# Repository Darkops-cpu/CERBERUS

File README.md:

# Cerberus

An open-source iCE40 FPGA development board with a fully open toolchain.

No licence server, no 100 GB install. Yosys, nextpnr and IceStorm run on any laptop and
synthesise a design this size in seconds.

> **Status:** rev A, first boards in fabrication. Untested. Do not fabricate your own copy
> until this note is gone.

---

## Features

| | |
|---|---|
| **FPGA** | Lattice iCE40UP5K — 5,280 LUT4, 120 kbit BRAM, 1 Mbit SPRAM, 8 DSP blocks |
| **PSRAM** | 8 MB QSPI (LY68L6400SLIT) |
| **Flash** | 4 MB SPI configuration flash (W25Q32) |
| **Host** | FT2232HL — USB programming *and* a serial console over one cable |
| **Clock** | 12 MHz active oscillator into a global clock buffer |
| **Expansion** | 2× PMOD, 8 user GPIO on a 0.1" header |
| **LEDs** | 3 user RGB + power, USB and CDONE status |
| **Connector** | USB-C |
| **PCB** | 4-layer, hand-assembled |

The FT2232H's two channels run independently, so you can flash a bitstream and watch a UART
console at the same time without switching modes.

---

## Getting started

### 1. Install the toolchain

Download the [OSS CAD Suite](https://github.com/YosysHQ/oss-cad-suite-build/releases) and
add it to your `PATH`. That's Yosys, nextpnr, IceStorm, Icarus, Verilator, GTKWave and
`iceprog` in one archive. Nothing to compile, nothing to licence.

```sh
source <path-to-oss-cad-suite>/environment
```

### 2. Build

```sh
yosys -p 'synth_ice40 -top top -json top.json' top.v
nextpnr-ice40 --up5k --package sg48 --json top.json --pcf cerberus.pcf --asc top.asc
icepack top.asc top.bin
```

### 3. Flash

The config SPI is on the FT2232H's **channel B**, so the `-I B` flag is required:

```sh
iceprog -I B top.bin
```

The CDONE LED lights when configuration succeeds.

### 4. Console

Channel A enumerates as a second serial port. On Linux the two channels appear as
`/dev/ttyUSB0` (A) and `/dev/ttyUSB1` (B):

```sh
picocom -b 115200 /dev/ttyUSB0
```

---

## Pinout

Key pins. Everything else is in `cerberus.pcf`.

| Function | FPGA pin |
|---|---|
| 12 MHz clock in | 37 (G1) |
| UART TX (FPGA → host) | 18 |
| UART RX (host → FPGA) | 19 |
| PSRAM CE# | 6 |
| PSRAM SCK | 9 |
| PSRAM SIO0–3 | 10, 11, 12, 13 |
| RGB LEDs | 39, 40, 41 |
| CDONE | 7 |
| CRESET_B | 8 |

Pins 14–17 are the configuration SPI bus and are not available to user designs.

**Globals available on this package:** 35 (G0), 37 (G1), 20 (G3), 44 (G6). Put clocks on
these — a clock on an ordinary pin routes through general fabric with worse skew.

**RGB LEDs** are constant-current sinks driven by the `SB_RGBA_DRV` primitive. Current is
set in the IP, not by a resistor.

---

## Notes

**Reset.** The button pulls `CRESET_B` low and reconfigures the FPGA from flash on release.
Configuration takes under 140 ms.

**Internal oscillator.** The iCE40's internal 48 MHz `SB_HFOSC` is ±20% on industrial parts.
Fine for blinking an LED, useless for a UART — that's why the board has an external
oscillator. Use pin 37.

**PSRAM.** The controller must break long transfers into chunks and deassert CE# between
them — the part self-refreshes only while CE# is high, and holding it low past the tCEM
window loses data. Linear burst across page boundaries is not supported on this part.

**Powering.** Bus-powered from USB-C. There is no barrel jack and no external supply input.

---

## Licence

Hardware: [CERN-OHL-S v2](https://cern-ohl.web.cern.ch/)
Gateware and examples: MIT

---

## Acknowledgements

Built on the work of [YosysHQ](https://github.com/YosysHQ) and
[Project IceStorm](https://github.com/YosysHQ/icestorm). Pin conventions follow
[iCEBreaker](https://github.com/icebreaker-fpga/icebreaker), and the SG48 pinout is
documented in Lattice FPGA-UG-02001.

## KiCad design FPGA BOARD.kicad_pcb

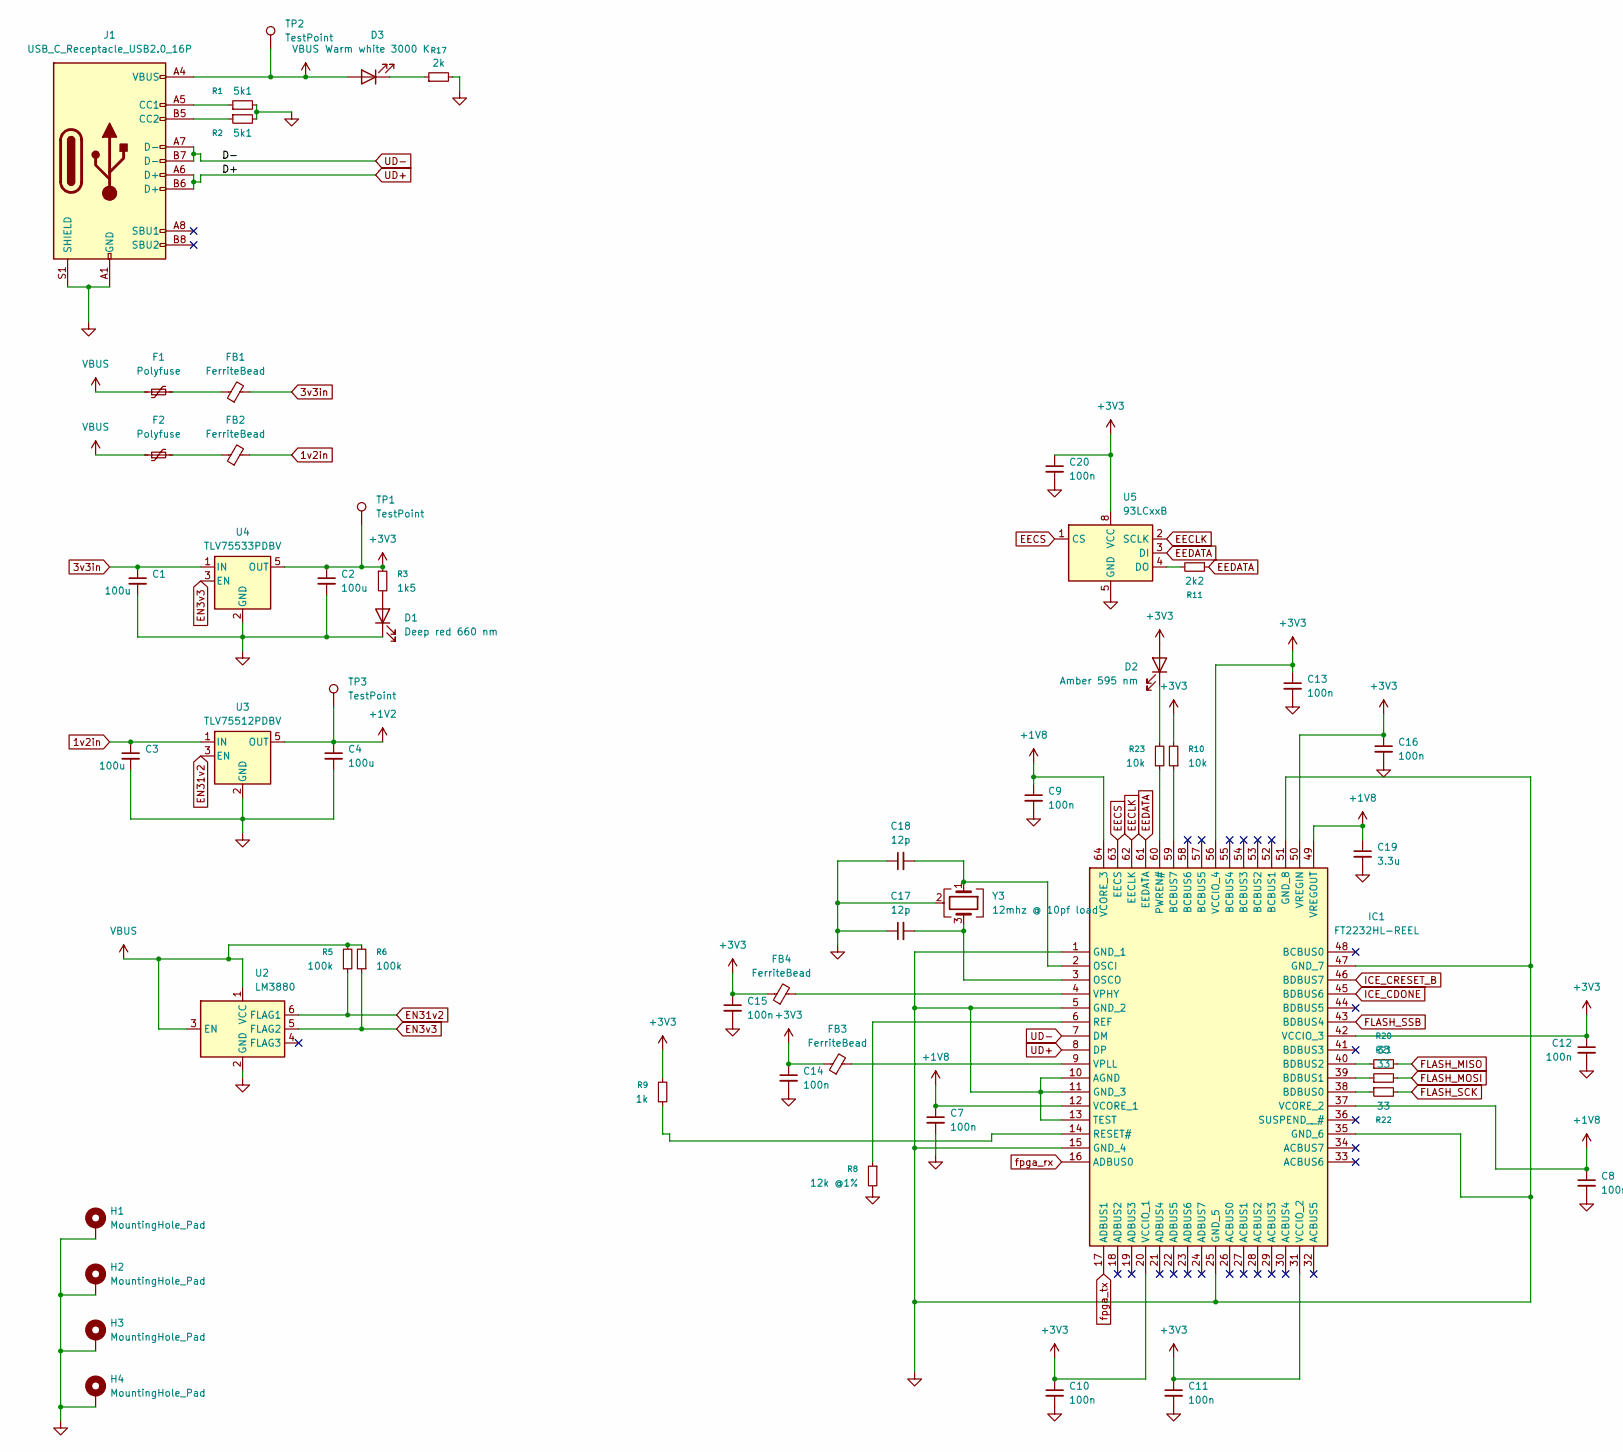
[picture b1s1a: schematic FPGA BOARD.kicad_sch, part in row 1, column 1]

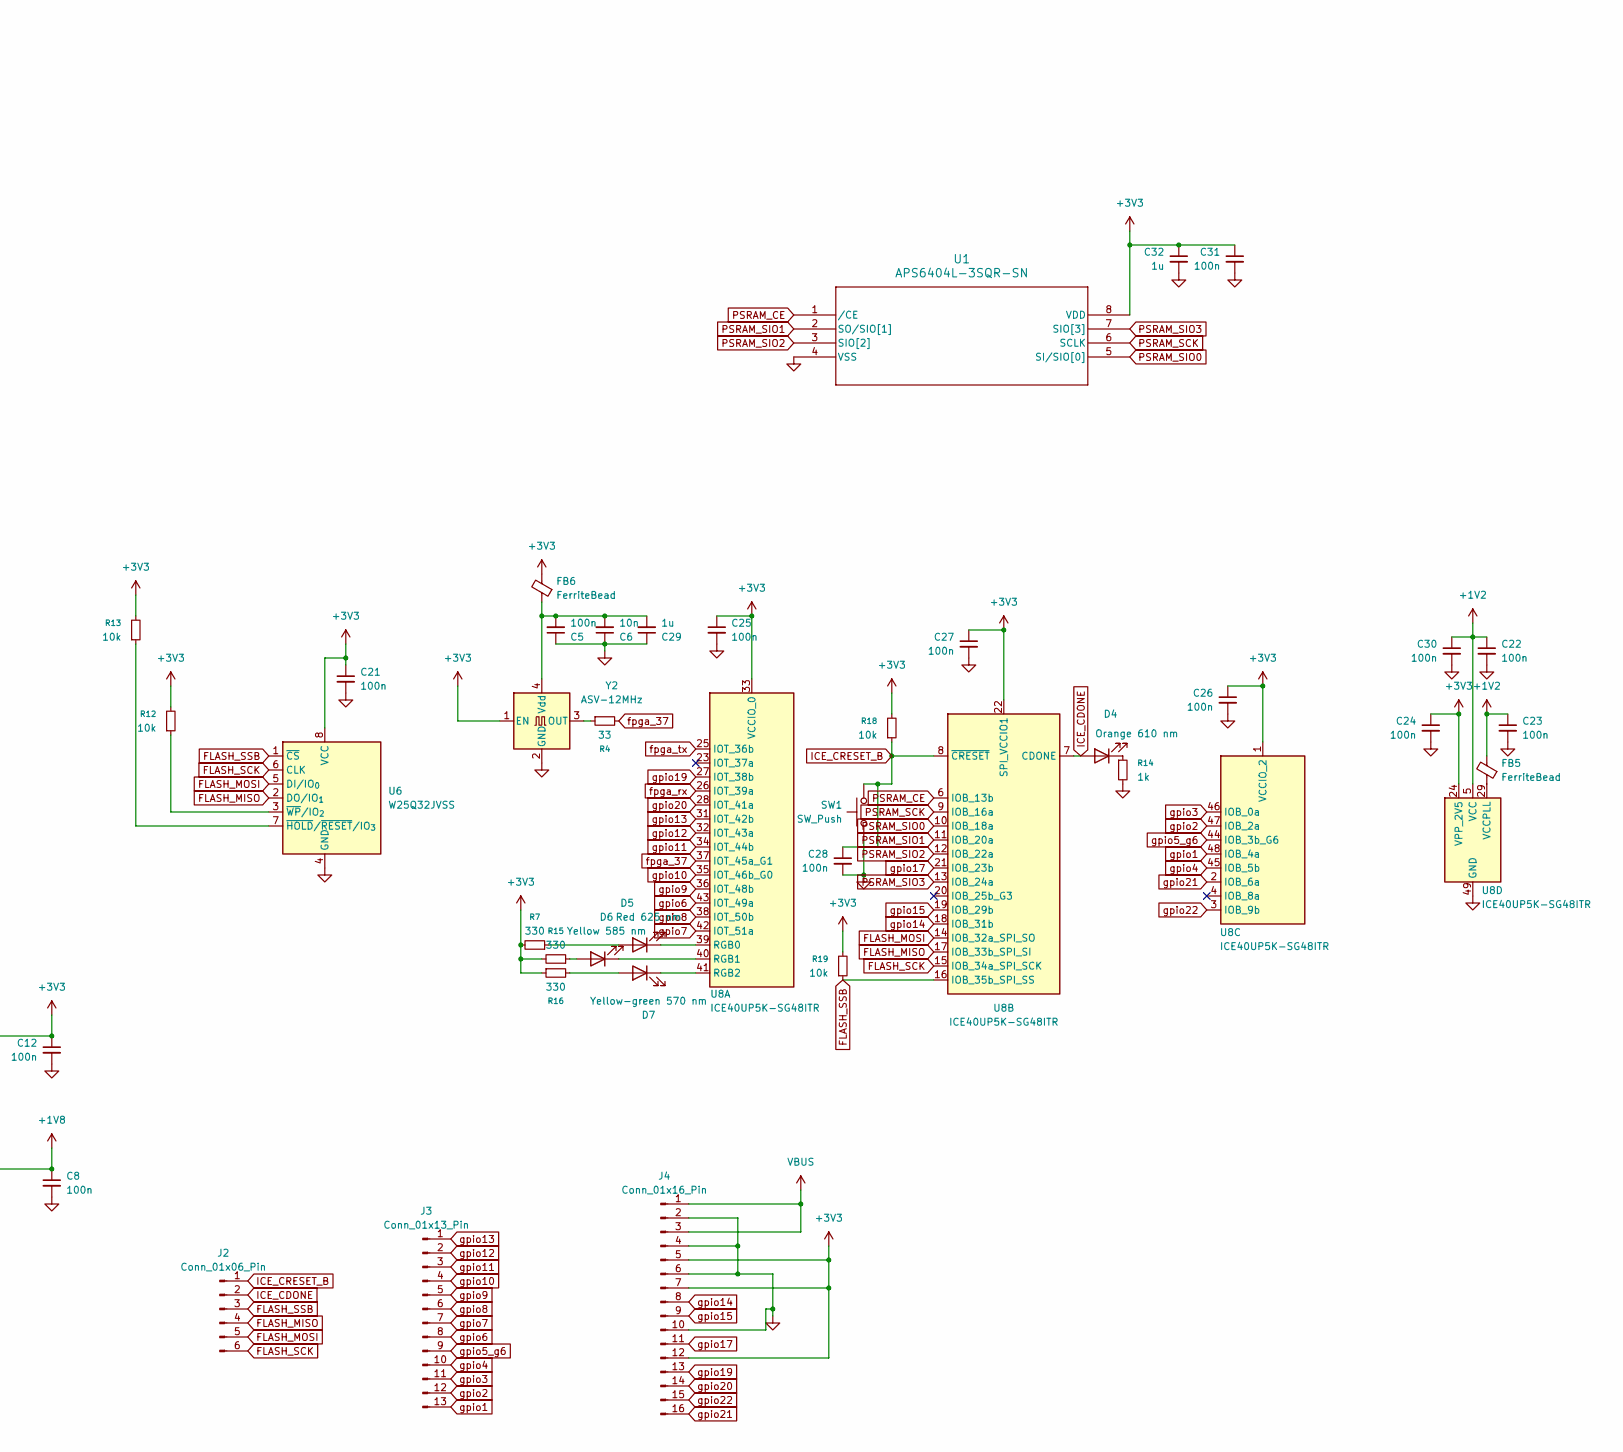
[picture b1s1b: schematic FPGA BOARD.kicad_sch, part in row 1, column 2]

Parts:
C1, C2, C3, C4: 100u; C_1210_3225Metric_Pad1.33x2.70mm_HandSolder
C5, C7, C8, C9, C10, C11, C12, C13, C14, C15, C16, C20, C21, C22, C23, C24, C25, C26, C27, C28, C30, C31: 100n; C_0603_1608Metric_Pad1.08x0.95mm_HandSolder
C6: 10n; C_0603_1608Metric_Pad1.08x0.95mm_HandSolder
C17, C18: 12p; C_0603_1608Metric_Pad1.08x0.95mm_HandSolder
C19: 3.3u; C_0603_1608Metric_Pad1.08x0.95mm_HandSolder
C29, C32: 1u; C_0603_1608Metric_Pad1.08x0.95mm_HandSolder
D1: Deep red 660 nm; LED_0603_1608Metric_Pad1.05x0.95mm_HandSolder
D2: Amber 595 nm; LED_0603_1608Metric_Pad1.05x0.95mm_HandSolder
D3: Warm white 3000 K; LED_0805_2012Metric_Pad1.15x1.40mm_HandSolder
D4: Orange 610 nm; LED_0603_1608Metric_Pad1.05x0.95mm_HandSolder
D5: Red 625 nm; LED_0603_1608Metric_Pad1.05x0.95mm_HandSolder
D6: Yellow 585 nm; LED_0603_1608Metric_Pad1.05x0.95mm_HandSolder
D7: Yellow-green 570 nm; LED_0603_1608Metric_Pad1.05x0.95mm_HandSolder
F1, F2: Polyfuse; R_0603_1608Metric_Pad0.98x0.95mm_HandSolder
FB1, FB2, FB3, FB4, FB5, FB6: FerriteBead; L_0603_1608Metric_Pad1.05x0.95mm_HandSolder
H1, H2, H3, H4: MountingHole_Pad; MountingHole_2.2mm_M2_Pad_Via
IC1: FT2232HL-REEL; QFP50P1200X1200X160-64N; Mouser Part Number 895-FT2232HL
J1: USB_C_Receptacle_USB2.0_16P; USB_C_Receptacle_GCT_USB4105-xx-A_16P_TopMnt_Horizontal
J2: Conn_01x06_Pin; PinHeader_1x06_P2.54mm_Vertical
J3: Conn_01x13_Pin; PinHeader_1x13_P2.54mm_Horizontal
J4: Conn_01x16_Pin; PinHeader_1x16_P2.54mm_Horizontal
R1, R2: 5k1; R_0603_1608Metric_Pad0.98x0.95mm_HandSolder
R3: 1k5; R_0603_1608Metric_Pad0.98x0.95mm_HandSolder
R4, R20, R21, R22: 33; R_0603_1608Metric_Pad0.98x0.95mm_HandSolder
R5, R6: 100k; R_0603_1608Metric_Pad0.98x0.95mm_HandSolder
R7, R15, R16: 330; R_0603_1608Metric_Pad0.98x0.95mm_HandSolder
R8: 12k @1%; R_0603_1608Metric_Pad0.98x0.95mm_HandSolder
R9, R14: 1k; R_0603_1608Metric_Pad0.98x0.95mm_HandSolder
R10, R12, R13, R18, R19, R23: 10k; R_0603_1608Metric_Pad0.98x0.95mm_HandSolder
R11: 2k2; R_0603_1608Metric_Pad0.98x0.95mm_HandSolder
R17: 2k; R_0603_1608Metric_Pad0.98x0.95mm_HandSolder
SW1: SW_Push; SW_Push_SPST_NO_Alps_SKRK
TP1, TP2, TP3: TestPoint; TestPoint_Pad_D1.5mm
U1: APS6404L-3SQR-SN; APS6404L-3SQR-SN_APY
U2: LM3880; SOT-23-6
U3: TLV75512PDBV; SOT-23-5
U4: TLV75533PDBV; SOT-23-5
U5: 93LCxxB; SOIC-8_3.9x4.9mm_P1.27mm
U6: W25Q32JVSS; SOIC-8_5.3x5.3mm_P1.27mm
U8: ICE40UP5K-SG48ITR; QFN-48-1EP_7x7mm_P0.5mm_EP5.6x5.6mm
Y2: ASV-12MHz; Oscillator_SMD_Abracon_ASV-4Pin_7.0x5.1mm
Y3: 12mhz @ 10pf load; Crystal_SMD_3225-4Pin_3.2x2.5mm

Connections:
1v2in: C3.1, FB2.2, U3.1 (IN)
3v3in: C1.1, FB1.2, U4.1 (IN)
+1V2: C4.1, C22.1, C23.1, C30.1, FB5.2, TP3.1, U3.5 (OUT), U8.5 (VCC), U8.30 (VCC)
+1V8: C7.1, C8.1, C9.1, C19.1, IC1.12 (VCORE_1), IC1.37 (VCORE_2), IC1.49 (VREGOUT), IC1.64 (VCORE_3)
+3V3: C2.1, C10.1, C11.1, C12.1, C13.1, C14.1, C15.1, C16.1, C20.1, C21.1, C24.1, C25.1, C26.1, C27.1, C31.1, C32.1, D2.2 (A), FB3.1, FB4.1, FB6.2, IC1.20 (VCCIO_1), IC1.31 (VCCIO_2), IC1.42 (VCCIO_3), IC1.50 (VREGIN), IC1.56 (VCCIO_4), J4.5, J4.7, J4.12, R3.1, R7.2, R9.2, R10.2, R12.2, R13.2, R15.2, R16.1, R18.2, R19.2, TP1.1, U1.8 (VDD), U4.5 (OUT), U5.8 (VCC), U6.8 (VCC), U8.1 (VCCIO_2), U8.22 (SPI_VCCIO1), U8.24 (VPP_2V5), U8.33 (VCCIO_0), Y2.1 (EN)
EECLK: IC1.62 (EECLK), U5.2 (SCLK)
EECS: IC1.63 (EECS), U5.1 (CS)
EEDATA: IC1.61 (EEDATA), R11.1, U5.3 (DI)
EN3v3: R6.1, U2.5 (FLAG2), U4.3 (EN)
EN31v2: R5.1, U2.6 (FLAG1), U3.3 (EN)
FLASH_MISO: J2.4, R20.2, U6.2 (DO/IO_{1}), U8.17 (IOB_33b_SPI_SI)
FLASH_MOSI: J2.5, R21.2, U6.5 (DI/IO_{0}), U8.14 (IOB_32a_SPI_SO)
FLASH_SCK: J2.6, R22.2, U6.6 (CLK), U8.15 (IOB_34a_SPI_SCK)
FLASH_SSB: IC1.43 (BDBUS4), J2.3, R19.1, U6.1 (~CS), U8.16 (IOB_35b_SPI_SS)
GND: C1.2, C2.2, C3.2, C4.2, C5.1, C6.1, C7.2, C8.2, C9.2, C10.2, C11.2, C12.2, C13.2, C14.2, C15.2, C16.2, C17.1, C18.1, C19.2, C20.2, C21.2, C22.2, C23.2, C24.2, C25.2, C26.2, C27.2, C28.2, C29.1, C30.2, C31.2, C32.2, D1.1 (K), H1.1, H2.1, H3.1, H4.1, IC1.1 (GND_1), IC1.5 (GND_2), IC1.10 (AGND), IC1.11 (GND_3), IC1.13 (TEST), IC1.15 (GND_4), IC1.25 (GND_5), IC1.35 (GND_6), IC1.47 (GND_7), IC1.51 (GND_8), J1.A1 (GND), J1.A12 (GND), J1.B1 (GND), J1.B12 (GND), J1.S1 (SHIELD), J4.2, J4.4, J4.6, J4.10, R1.2, R2.2, R8.2, R14.2, R17.2, SW1.1, U1.4 (VSS), U2.2 (GND), U3.2 (GND), U4.2 (GND), U5.5 (GND), U6.4 (GND), U8.49 (GND), Y2.2 (GND), Y3.2 (G), Y3.4 (G)
ICE_CDONE: D4.2 (A), IC1.45 (BDBUS6), J2.2, U8.7 (CDONE)
ICE_CRESET_B: C28.1, IC1.46 (BDBUS7), J2.1, R18.1, SW1.2, U8.8 (~CRESET)
unnamed: D1.2 (A), R3.2
unnamed: D2.1 (K), R23.2
unnamed: D3.1 (K), R17.1
unnamed: D4.1 (K), R14.1
unnamed: D5.2 (A), R7.1
unnamed: D5.1 (K), U8.39 (RGB0)
unnamed: D6.2 (A), R15.1
unnamed: D6.1 (K), U8.40 (RGB1)
unnamed: D7.2 (A), R16.2
unnamed: D7.1 (K), U8.41 (RGB2)
unnamed: F1.2, FB1.1
unnamed: F2.2, FB2.1
unnamed: IC1.59 (BCBUS7), R10.1
unnamed: IC1.38 (BDBUS0), R22.1
unnamed: IC1.39 (BDBUS1), R21.1
unnamed: IC1.40 (BDBUS2), R20.1
unnamed: C18.2, IC1.2 (OSCI), Y3.1
unnamed: C17.2, IC1.3 (OSCO), Y3.3
unnamed: IC1.60 (PWREN#), R23.1
unnamed: IC1.6 (REF), R8.1
unnamed: IC1.14 (RESET#), R9.1
unnamed: FB4.2, IC1.4 (VPHY)
unnamed: FB3.2, IC1.9 (VPLL)
unnamed: J1.A5 (CC1), R1.1
unnamed: J1.B5 (CC2), R2.1
unnamed: R11.2, U5.4 (DO)
unnamed: R13.1, U6.7 (~HOLD/~RESET/IO_{3})
unnamed: R12.1, U6.3 (~WP/IO_{2})
unnamed: FB5.1, U8.29 (VCCPLL)
unnamed: R4.1, Y2.3 (OUT)
unnamed: C5.2, C6.2, C29.2, FB6.1, Y2.4 (Vdd)
PSRAM_CE: U1.1 (/CE), U8.6 (IOB_13b)
PSRAM_SCK: U1.6 (SCLK), U8.9 (IOB_16a)
PSRAM_SIO0: U1.5 (SI/SIO[0]), U8.10 (IOB_18a)
PSRAM_SIO1: U1.2 (SO/SIO[1]), U8.11 (IOB_20a)
PSRAM_SIO2: U1.3 (SIO[2]), U8.12 (IOB_22a)
PSRAM_SIO3: U1.7 (SIO[3]), U8.13 (IOB_24a)
UD+: IC1.8 (DP), J1.A6 (D+), J1.B6 (D+)
UD-: IC1.7 (DM), J1.A7 (D-), J1.B7 (D-)
VBUS: D3.2 (A), F1.1, F2.1, J1.A4 (VBUS), J1.A9 (VBUS), J1.B4 (VBUS), J1.B9 (VBUS), J4.1, J4.3, R5.2, R6.2, TP2.1, U2.1 (VCC), U2.3 (EN)
fpga_37: R4.2, U8.37 (IOT_45a_G1)
fpga_rx: IC1.16 (ADBUS0), U8.26 (IOT_39a)
fpga_tx: IC1.17 (ADBUS1), U8.25 (IOT_36b)
gpio1: J3.13, U8.48 (IOB_4a)
gpio2: J3.12, U8.47 (IOB_2a)
gpio3: J3.11, U8.46 (IOB_0a)
gpio4: J3.10, U8.45 (IOB_5b)
gpio5_g6: J3.9, U8.44 (IOB_3b_G6)
gpio6: J3.8, U8.43 (IOT_49a)
gpio7: J3.7, U8.42 (IOT_51a)
gpio8: J3.6, U8.38 (IOT_50b)
gpio9: J3.5, U8.36 (IOT_48b)
gpio10: J3.4, U8.35 (IOT_46b_G0)
gpio11: J3.3, U8.34 (IOT_44b)
gpio12: J3.2, U8.32 (IOT_43a)
gpio13: J3.1, U8.31 (IOT_42b)
gpio14: J4.8, U8.18 (IOB_31b)
gpio15: J4.9, U8.19 (IOB_29b)
gpio17: J4.11, U8.21 (IOB_23b)
gpio19: J4.13, U8.27 (IOT_38b)
gpio20: J4.14, U8.28 (IOT_41a)
gpio21: J4.16, U8.2 (IOB_6a)
gpio22: J4.15, U8.3 (IOB_9b)

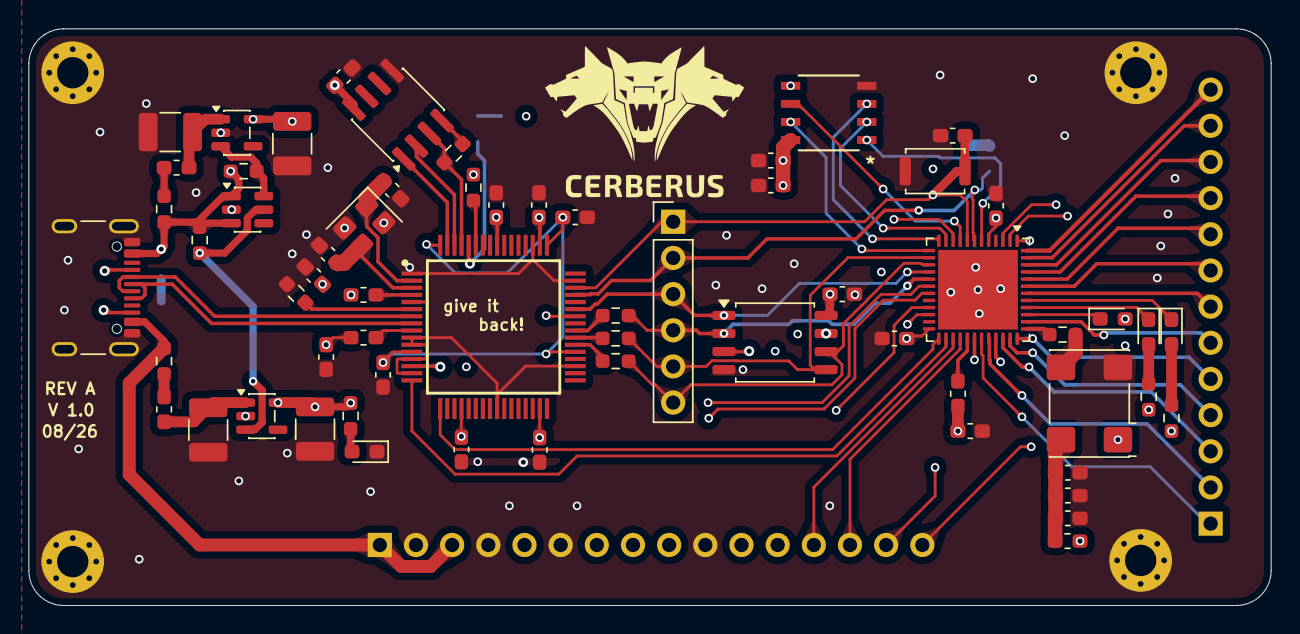
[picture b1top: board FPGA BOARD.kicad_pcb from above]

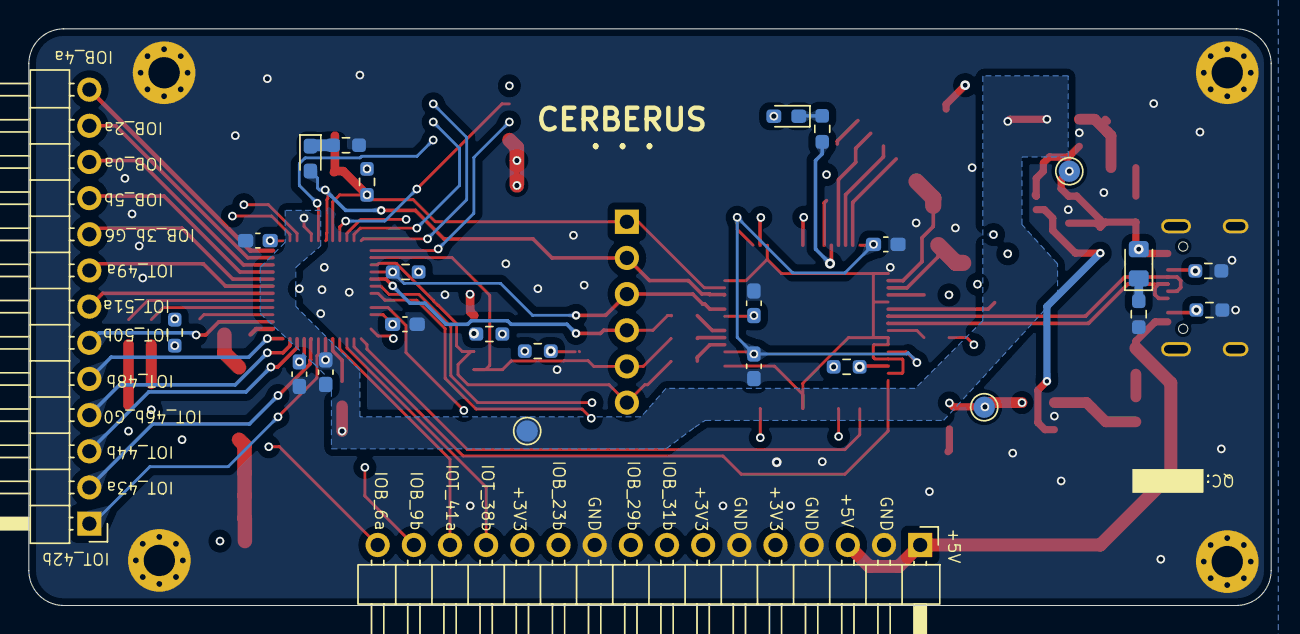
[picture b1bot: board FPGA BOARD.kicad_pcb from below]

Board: 4 copper layers, 87.2 x 40.5 mm, 92 parts (26 on the bottom side), 80 nets.

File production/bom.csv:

Designator,Footprint,Quantity,Value,LCSC Part #
"C1, C2, C3, C4",1210,4,100u,
"C10, C11, C12, C13, C14, C15, C16, C20, C21, C22, C23, C24, C25, C26, C27, C28, C30, C31, C5, C7, C8, C9",0603,22,100n,
"C17, C18",0603,2,12p,
C19,0603,1,3.3u,
"C29, C32",0603,2,1u,
C6,0603,1,10n,
D1,0603,1,Deep red 660 nm,
D2,0603,1,Amber 595 nm,
D3,0805,1,Warm white 3000 K,
D4,0603,1,Orange 610 nm,
D5,0603,1,Red 625 nm,
D6,0603,1,Yellow 585 nm,
D7,0603,1,Yellow-green 570 nm,
"F1, F2",0603,2,Polyfuse,
"FB1, FB2, FB3, FB4, FB5, FB6",0603,6,FerriteBead,
IC1,QFP50P1200X1200X160-64N,1,FT2232HL-REEL,
J1,USB_C_Receptacle_GCT_USB4105-xx-A_16P_TopMnt_Horizontal,1,USB_C_Receptacle_USB2.0_16P,
J2,PinHeader_1x06_P2.54mm_Vertical,1,Conn_01x06_Pin,
J3,PinHeader_1x13_P2.54mm_Horizontal,1,Conn_01x13_Pin,
J4,PinHeader_1x16_P2.54mm_Horizontal,1,Conn_01x16_Pin,
"R1, R2",0603,2,5k1,
"R10, R12, R13, R18, R19, R23",0603,6,10k,
R11,0603,1,2k2,
"R14, R9",0603,2,1k,
"R15, R16, R7",0603,3,330,
R17,0603,1,2k,
"R20, R21, R22, R4",0603,4,33,
R3,0603,1,1k5,
"R5, R6",0603,2,100k,
R8,0603,1,12k @1%,
SW1,SW_Push_SPST_NO_Alps_SKRK,1,SW_Push,
"TP1, TP2, TP3",TestPoint_Pad_D1.5mm,3,TestPoint,
U1,APS6404L-3SQR-SN_APY,1,APS6404L-3SQR-SN,
U2,SOT-23-6,1,LM3880,
U3,SOT-23-5,1,TLV75512PDBV,
U4,SOT-23-5,1,TLV75533PDBV,
U5,SOIC-8_3.9x4.9mm_P1.27mm,1,93LCxxB,
U6,SOIC-8_5.3x5.3mm_P1.27mm,1,W25Q32JVSS,
U8,QFN-48-1EP_7x7mm_P0.5mm_EP5.6x5.6mm,1,ICE40UP5K-SG48ITR,
Y2,Oscillator_SMD_Abracon_ASV-4Pin_7.0x5.1mm,1,ASV-12MHz,
Y3,Crystal_SMD_3225-4Pin_3.2x2.5mm,1,12mhz @ 10pf load,
